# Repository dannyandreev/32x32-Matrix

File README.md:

Setup from clean Windows:
Install Git: https://gitforwindows.org/
Install VSCode: https://code.visualstudio.com/Download
Install Python: https://www.python.org/downloads/release/python-3121/
Debug PIP: https://stackoverflow.com/questions/37220055/pip-fatal-error-in-launcher-unable-to-create-process-using
Install MicroPython: https://docs.micropython.org/en/latest/esp32/tutorial/intro.html
Install Pymakr: https://lemariva.com/blog/2018/12/micropython-visual-studio-code-as-ide#:~:text=To%20use%20VSCode%20for%20MicroPython,build%2Din%20command%20line%20REPL.
Install Node: https://nodejs.org/en/
Install esptool: https://docs.espressif.com/projects/esptool/en/latest/esp32/installation.html
Get the ESP Working: https://hackmd.io/@lnu-iot/SJASdMCo_
Install ESP32 drivers: https://www.silabs.com/developers/usb-to-uart-bridge-vcp-drivers)https://www.silabs.com/developers/usb-to-uart-bridge-vcp-drivers
Useful Blink tutorial: https://www.youtube.com/watch?v=YOeV14SESls&ab_channel=DonskyTech
Install microPython on your ESP32: https://medium.com/@ivanzhd/flash-micropython-to-an-esp32-board-using-mackr-in-vscode-479f2504e2d0#:~:text=Connect%20your%20ESP32%20board%20to,the%20list%20of%20available%20boards.

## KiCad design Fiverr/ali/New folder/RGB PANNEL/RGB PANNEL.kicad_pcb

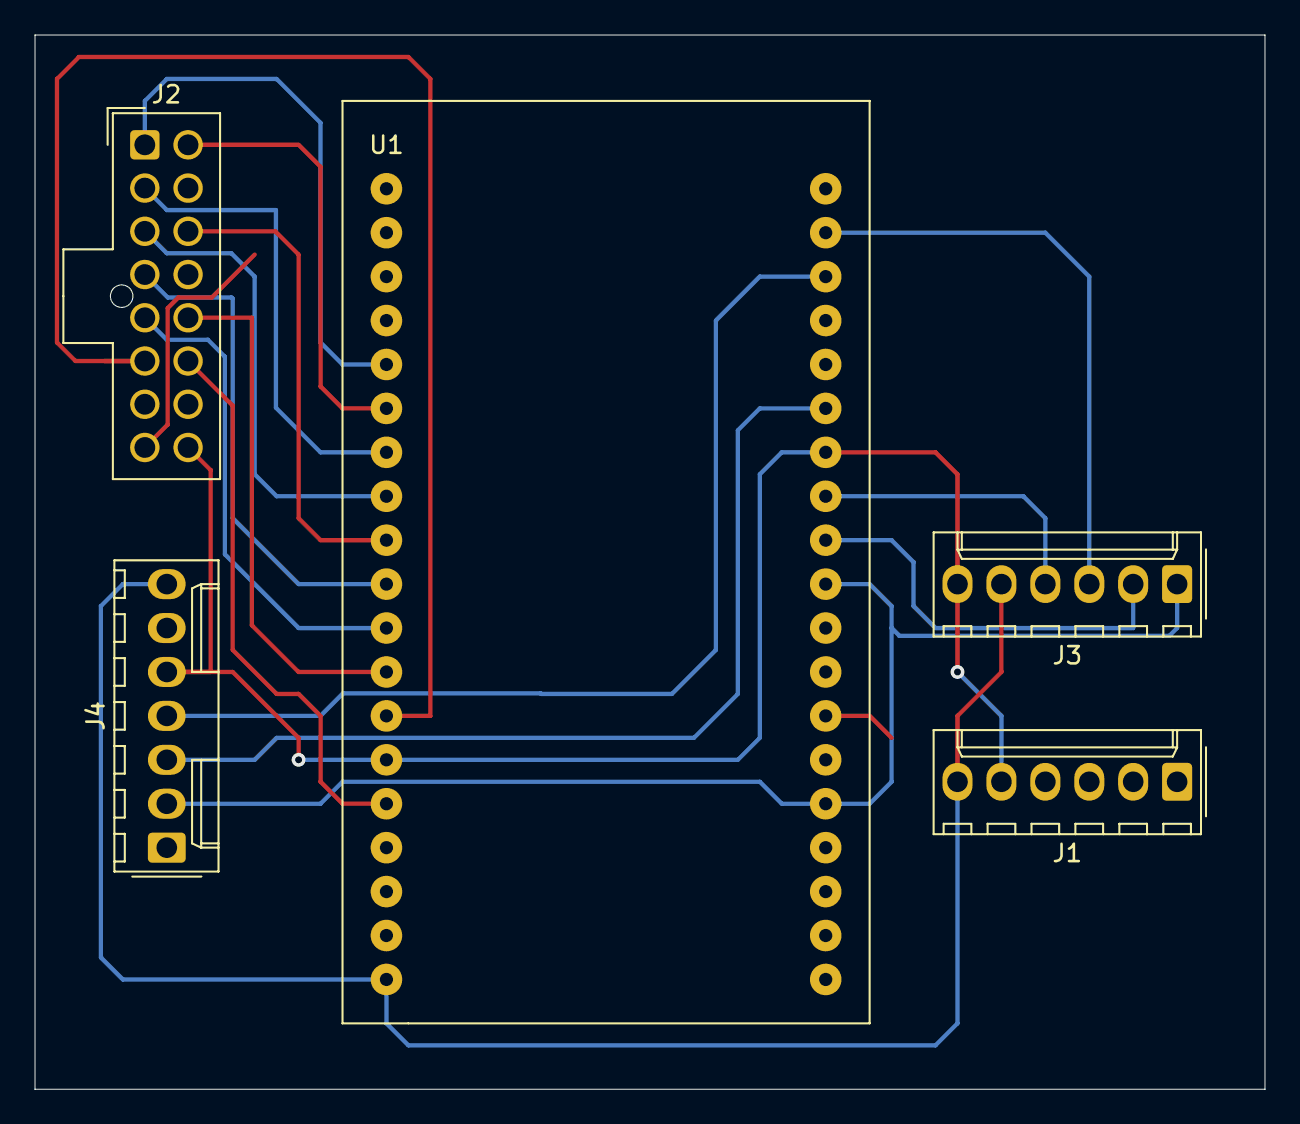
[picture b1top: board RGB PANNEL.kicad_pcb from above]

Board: 2 copper layers, 71.1 x 61.0 mm, 5 parts (0 on the bottom side), 21 nets.

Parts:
J1: Conn_01x06; Molex_KK-254_AE-6410-06A_1x06_P2.54mm_Vertical
J2: DISPLAY MODULE; Molex_Nano-Fit_105310-xx16_2x08_P2.50mm_Vertical
J3: SD CARD MODULE; Molex_KK-254_AE-6410-06A_1x06_P2.54mm_Vertical
J4: LSM6DS3; Molex_KK-254_AE-6410-07A_1x07_P2.54mm_Vertical
U1: ESP32S; ESP

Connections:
5V: J1.6, J3.5, J4.7, U1.19 (V5)
A: J2.5, U1.11 (D27)
B: J2.12, U1.12 (D14)
B1: J2.2, U1.7 (D32)
B2: J2.4, U1.10 (D26)
C: J2.6, U1.13 (D12)
CLK: J2.7, U1.28 (D17)
CS: J3.1, J4.2, U1.24 (D2), U1.29 (D5)
G1: J2.16, U1.6 (D35)
G2: J2.14, U1.9 (D25)
GND: J1.5, J2.9, J2.13, J2.15, J3.6, J4.5, U1.14 (GND), U1.32 (GND), U1.38 (GND)
MISO: J3.4, U1.31 (D19)
MOSI: J3.3, U1.37 (D23)
OE: J2.8, U1.26 (D4)
R1: J2.1, U1.5 (D34)
R2: J2.3, U1.8 (D33)
SCK: J3.2, U1.30 (D18)
SCL: J4.4, U1.36 (D22)
SDA: J4.3, U1.33 (D21)
STB: J2.10, U1.27 (D16)
d: J2.11, U1.15 (D13)

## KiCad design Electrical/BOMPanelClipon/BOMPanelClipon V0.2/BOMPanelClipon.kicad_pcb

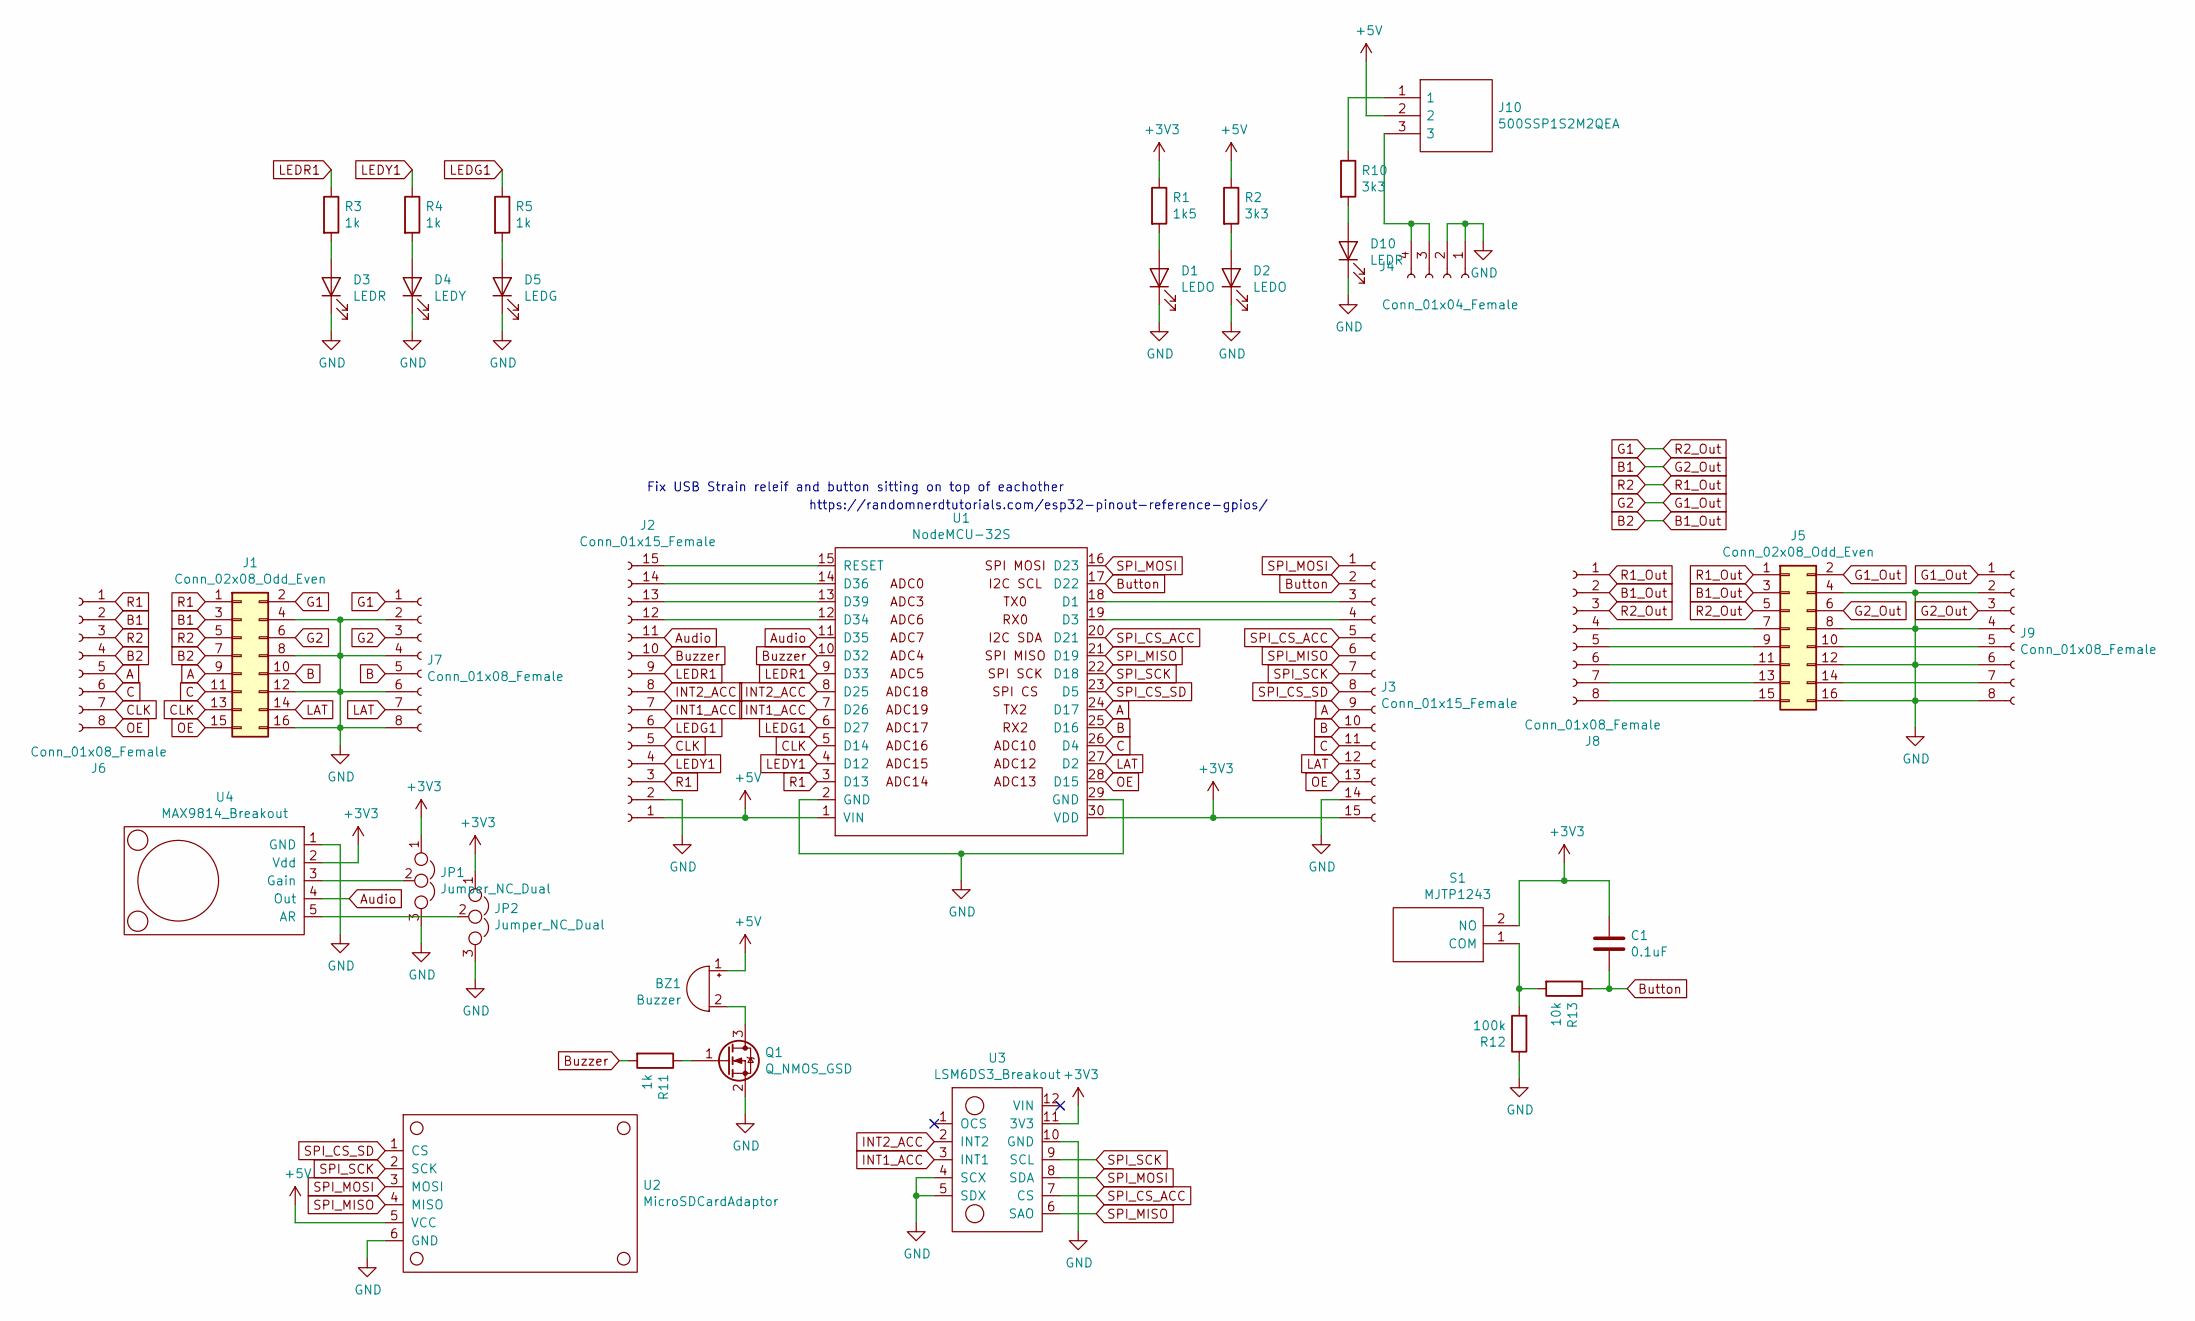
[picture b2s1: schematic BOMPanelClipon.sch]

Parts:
BZ1: Buzzer; Buzzer_12x9.5RM7.6
C1: 0.1uF; C_0805_2012Metric
D1, D2: LEDO; D_0805_2012Metric
D3, D10: LEDR; D_0805_2012Metric
D4: LEDY; D_0805_2012Metric
D5: LEDG; D_0805_2012Metric
J1, J5: Conn_02x08_Odd_Even; PinSocket_2x08_P2.54mm_Vertical
J2, J3: Conn_01x15_Female; PinSocket_1x15_P2.54mm_Vertical
J4: Conn_01x04_Female; Conn_4pin_3.96mm_0009483046
J6, J7, J8, J9: Conn_01x08_Female; PinSocket_1x08_P2.54mm_Vertical
J10: 500SSP1S2M2QEA; Manufacturer_Part_Number 500SSP1S2M2QEA; Mouser Part Number 612-500SSP1S2M2QEA
JP1, JP2: Jumper_NC_Dual; PinHeader_1x03_P2.54mm_Vertical
Q1: Q_NMOS_GSD; SOT-23_Handsoldering
R1: 1k5; R_0805_2012Metric
R2, R10: 3k3; R_0805_2012Metric
R3, R4, R5, R11: 1k; R_0805_2012Metric
R12: 100k; R_0805_2012Metric
R13: 10k; R_0805_2012Metric
S1: MJTP1243; Manufacturer_Part_Number MJTP1243; Mouser Part Number 642-MJTP1243
U1: NodeMCU-32S; NODEMCU-32S_ESP32
U2: MicroSDCardAdaptor; MicroSDCardAdapter
U3: LSM6DS3_Breakout
U4: MAX9814_Breakout

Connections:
+3V3: C1.1, J3.15, JP1.1, JP2.1, R1.1, S1.2 (NO), U1.30 (VDD), U3.11 (3V3), U4.2 (Vdd)
+5V: BZ1.1 (-), J2.1, J10.2, R2.1, U1.1 (VIN), U2.5 (VCC)
A: J1.9, J3.9, J6.5, U1.24 (D17)
Audio: J2.11, U1.11 (D35), U4.4 (Out)
B: J1.10, J3.10, J7.5, U1.25 (D16)
B1: J1.3, J5.6, J6.2, J9.3
B1_Out: J1.7, J5.3, J6.4, J8.2
Button: C1.2, J3.2, R13.1, U1.17 (D22)
Buzzer: J2.10, R11.2, U1.10 (D32)
C: J1.11, J3.11, J6.6, U1.26 (D4)
CLK: J1.13, J2.5, J6.7, U1.5 (D14)
G1: J1.2, J5.5, J7.1, J8.3
G1_Out: J1.6, J5.2, J7.3, J9.1
GND: D1.1 (K), D2.1 (K), D3.1 (K), D4.1 (K), D5.1 (K), D10.1 (K), J1.4, J1.8, J1.12, J1.16, J2.2, J3.14, J4.1, J4.2, J5.4, J5.8, J5.12, J5.16, J7.2, J7.4, J7.6, J7.8, J9.2, J9.4, J9.6, J9.8, JP1.3, JP2.3, Q1.2 (S), R12.1, U1.2 (GND), U1.29 (GND), U2.6 (GND), U3.4 (SCX), U3.5 (SDX), U3.10 (GND), U4.1 (GND)
INT1_ACC: J2.7, U1.7 (D26), U3.3 (INT1)
INT2_ACC: J2.8, U1.8 (D25), U3.2 (INT2)
LAT: J1.14, J3.12, J7.7, U1.27 (D2)
LEDG1: J2.6, R5.1, U1.6 (D27)
LEDR1: J2.9, R3.1, U1.9 (D33)
LEDY1: J2.4, R4.1, U1.4 (D12)
unnamed: BZ1.2 (+), Q1.3 (D)
unnamed: D1.2 (A), R1.2
unnamed: D2.2 (A), R2.2
unnamed: D3.2 (A), R3.2
unnamed: D4.2 (A), R4.2
unnamed: D5.2 (A), R5.2
unnamed: D10.2 (A), R10.2
unnamed: J2.12, U1.12 (D34)
unnamed: J2.13, U1.13 (D39)
unnamed: J2.14, U1.14 (D36)
unnamed: J2.15, U1.15 (RESET)
unnamed: J3.3, U1.18 (D1)
unnamed: J3.4, U1.19 (D3)
unnamed: J5.7, J8.4
unnamed: J5.9, J8.5
unnamed: J5.10, J9.5
unnamed: J5.11, J8.6
unnamed: J5.13, J8.7
unnamed: J5.14, J9.7
unnamed: J5.15, J8.8
unnamed: J10.1, R10.1
unnamed: J4.3, J4.4, J10.3
unnamed: JP1.2, U4.3 (Gain)
unnamed: JP2.2, U4.5 (AR)
unnamed: Q1.1 (G), R11.1
unnamed: R12.2, R13.2, S1.1 (COM)
OE: J1.15, J3.13, J6.8, U1.28 (D15)
R1: J1.1, J2.3, J6.1, U1.3 (D13)
R1_Out: J1.5, J5.1, J6.3, J8.1
SPI_CS_ACC: J3.5, U1.20 (D21), U3.7 (CS)
SPI_CS_SD: J3.8, U1.23 (D5), U2.1 (CS)
SPI_MISO: J3.6, U1.21 (D19), U2.4 (MISO), U3.6 (SAO)
SPI_MOSI: J3.1, U1.16 (D23), U2.3 (MOSI), U3.8 (SDA)
SPI_SCK: J3.7, U1.22 (D18), U2.2 (SCK), U3.9 (SCL)

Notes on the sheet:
Fix USB Strain releif and button sitting on top of eachother
https://randomnerdtutorials.com/esp32-pinout-reference-gpios/

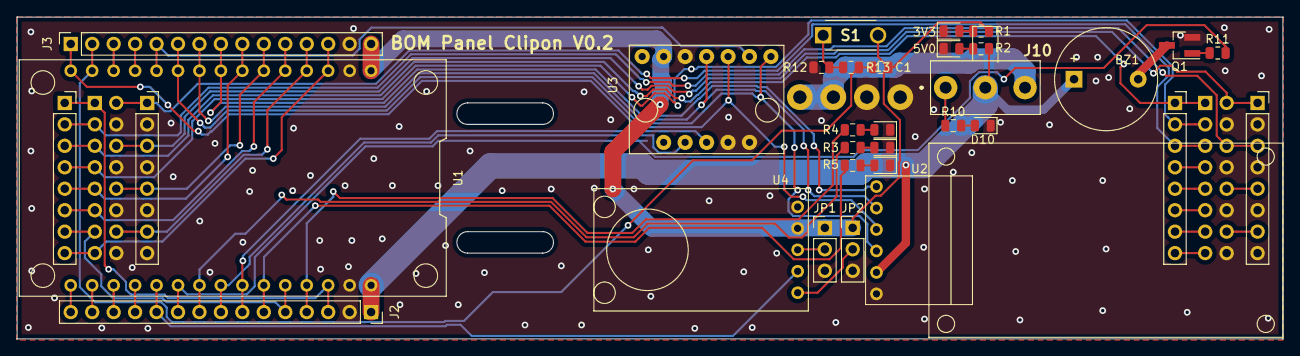
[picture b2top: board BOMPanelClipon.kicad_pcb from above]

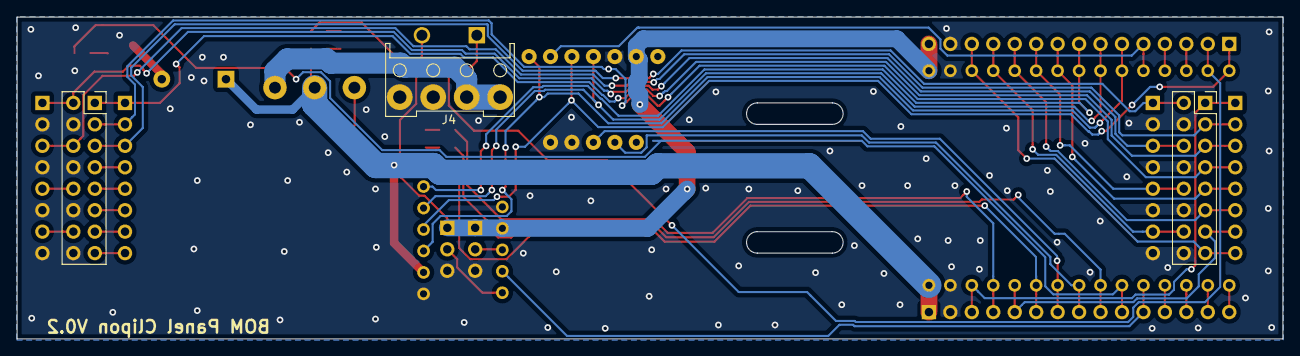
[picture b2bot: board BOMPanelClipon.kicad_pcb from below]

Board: 2 copper layers, 149.9 x 38.1 mm, 35 parts (3 on the bottom side), 54 nets.

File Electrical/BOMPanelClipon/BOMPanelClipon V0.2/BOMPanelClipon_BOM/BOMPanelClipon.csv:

Id,Designator,Package,Quantity,Designation,Supplier and ref,Notes
1,U4,MAX9814_Breakout,1,MAX9814_Breakout,PTC051LFBN-RC? ,
2,J4,None,0,None,None,None
3,"J7,J6,J8,J9",None,0,None,None,None
4,C1,C_0805_2012Metric,1,0.1uF,885012207072,
5,R13,R_0805_2012Metric,1,10k,CRCW080510K0FKEAC,
6,R12,R_0805_2012Metric,1,100k,CRCW0805100KFKEAC,
7,U2,MicroSDCardAdapter,1,MicroSDCardAdaptor,PPPC061LGBN-RC ,
8,U1,NODEMCU-32S_ESP32,1,NodeMCU-32S,2 x ?PPTC151LFBN-RC?,2 separate parts are needed for this device
9,U3,LSM6DS3_Breakout,1,LSM6DS3_Breakout,"1 x ?PPTC051LFBN-RC?
?1 x PPTC071LFBN-RC",2 separate parts are needed for this device
10,"D1,D2",D_0805_2012Metric,2,LEDO,L171L-QOC ,
11,D5,D_0805_2012Metric,1,LEDG,L171L-GC ,
12,"J1,J5",PinSocket_2x08_P2.54mm_Vertical,2,Conn_02x08_Odd_Even,ESQ-108-12-L-D ,
13,"J2,J3",None,0,None,None,None
14,R1,R_0805_2012Metric,1,1k5,CRCW08051K50FKEAC,
15,"R2,R10",R_0805_2012Metric,2,3k3,CRCW08053K30FKEAC,
16,"R5,R3,R4,R11",R_0805_2012Metric,4,1k,CRCW08051K00JNEAC,
17,BZ1,Buzzer_12x9.5RM7.6,1,Buzzer,2056-MB12-5V-ND,
18,"D3,D10",D_0805_2012Metric,2,LEDR,L171L-LIC ,
19,D4,D_0805_2012Metric,1,LEDY,L171L-YC ,
20,"JP1,JP2",PinHeader_1x03_P2.54mm_Vertical,2,Jumper_NC_Dual,75160-156-03LF ,
21,Q1,SOT-23_Handsoldering,1,Q_NMOS_GSD,DMN2075U-7 ,
22,S1,MJTP1243,1,MJTP1243,MJTP1243 ,
23,J10,500SSP1S2M2QEA,1,500SSP1S2M2QEA,500SSP1S2M2QEA ,

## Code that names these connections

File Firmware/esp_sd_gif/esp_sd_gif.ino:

#include "FS.h"
#include "SD.h"
#include "SPI.h"
#include "stdio.h"
#include <Ticker.h>
#include <PxMatrix.h>

Ticker display_ticker;
File root;

#define LEDG1 36
#define LEDG2 39
#define LEDG3 34
#define LEDG4 1
#define LEDG5 3

#define LEDR1 33
#define LEDY1 12

#define Buzzer 32

// Pins for LED MATRIX // changed from default
#define P_LAT 2
#define P_A 17
#define P_B 16
#define P_C 4
#define P_OE 15

#define MAXGIF 12

PxMATRIX display(32, 32, P_LAT, P_OE,P_A,P_B,P_C); // changed from default

uint16_t images[MAXGIF][1024];
bool sdRead = false;

// ISR for display refresh
void display_updater()
{
  display.display(10);
}

 // Array to store the pixels

void readFile(fs::FS &fs, const char * path, uint16_t images[MAXGIF][1024], int num){

  char pixel[20];
  char inputChar;
  int stringIndex = 2;
  int idx = -1;
  int imageIdx = 0;
  
//    Serial.printf("Reading file: %s\n", path);

    File file = fs.open(path);
    if(!file){
        Serial.println("Failed to open file for reading");
        return;
    }
    
  while (file.available()) {

    inputChar = file.read();

    if (inputChar == 'x') { // new hex value
      idx = 0;
    }

    else  { // not a hex trigger

      if (idx > -1) { // currently writing a pixel
        
        if (idx == 4) { // finished writing pixel
          

          if (inputChar == ',') { // correct pixel
            idx = -1;
            images[num][imageIdx] = (uint16_t) strtol(pixel, NULL, 16);
            imageIdx++;
          }

          else { // not a correct pixel
            idx = -1;
          }

        }

        else { // not done writing pixel
          if ((inputChar >= '0' && inputChar <= '9') || 
          (inputChar >= 'a' && inputChar <= 'f')) { // correct character for pixel
            pixel[idx] = inputChar;
            idx++;
          }

          else { // incorrect character for pixel
            idx = -1;
          }
        }

      }
    }
  }
    file.close();
    
//    for (int i = 0; i < 1024; i++) {
//      Serial.println(image[i], HEX);
//    }
}

void setup() {

    pinMode(LEDG1, OUTPUT);
    pinMode(LEDG2, OUTPUT);
    pinMode(LEDG3, OUTPUT);
    pinMode(LEDG4, OUTPUT);
    pinMode(LEDG5, OUTPUT);

    pinMode(LEDR1, OUTPUT);
    pinMode(LEDY1, OUTPUT);

    pinMode(Buzzer, OUTPUT);
  
    Serial.begin(115200);
    
    if(!SD.begin()){
        Serial.println("Card Mount Failed");
        return;
    }

    sdRead = true;

      root = SD.open("/");
      const int fCounter = countFiles(root, images);

      for (int i = 0; i < MAXGIF; i++) {
        //Serial.println("~~~~~~~~~~~next~~~~~~~~~~");
        for (int j = 0; j < 1024; j++) {
          if(j%16==0){
            Serial.println();
          }
          //Serial.print(" ");
          //Serial.print(images[i][j], HEX);
        }
      }

    // necessary for panel to work after reading from SD card
    SPI.end();


  display.begin(8, 14, 13, 5, 23);
  display.clearDisplay();
  display_ticker.attach(0.002, display_updater);
  yield();

}

void drawAllFrames(uint16_t images[MAXGIF][1024]) {
  for (int i = 0; i < MAXGIF; i++) {
    drawFrame(images[i]);
  }
  yield();
}

void loop() {
  // put your main code here, to run repeatedly:
  if (sdRead) {
     drawAllFrames(images);
  }
}

void drawFrame(uint16_t *frame) {
  display.clearDisplay();
  int imageHeight = 32;
  int imageWidth = 32;
  int counter = 0;
  for (int yy = 0; yy < imageHeight; yy++) {
    for (int xx = 0; xx < imageWidth; xx++) {
      display.drawPixel(xx, yy, frame[counter]);
      counter++;
    }
  }
  delay(100);
}

int countFiles(File dir, uint16_t images[MAXGIF][1024]) {

  int counter = 0;

  while (true) {

    File entry =  dir.openNextFile();

    if (!entry) { // no more files
      
      break;
      
    }

    String fileName = entry.name();

    if ((fileName.endsWith(".c") || fileName.endsWith(".C")) && !fileName.startsWith("/._")) {
      Serial.println(fileName.c_str());
      readFile(SD, fileName.c_str(), images, counter);
      counter++;
    }

    entry.close();

  }
  return counter;
}

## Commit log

2024-01-27 platformio
